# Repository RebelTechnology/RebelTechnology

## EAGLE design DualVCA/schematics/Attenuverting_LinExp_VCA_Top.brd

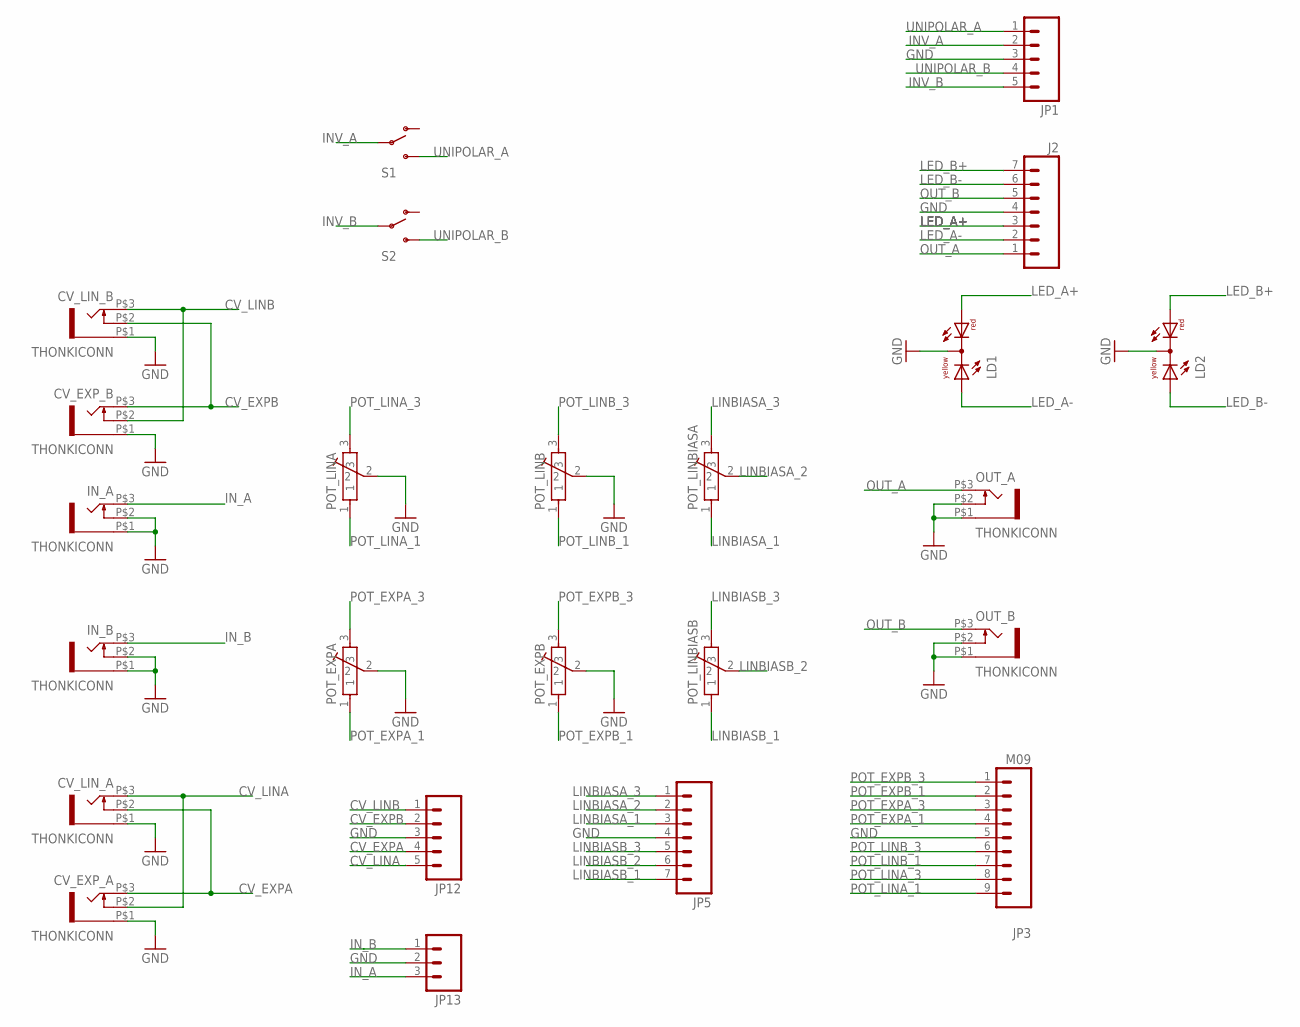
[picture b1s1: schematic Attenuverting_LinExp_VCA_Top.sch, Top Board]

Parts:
CV_EXP_A: THONKICONN
CV_EXP_B: THONKICONN
CV_LIN_A: THONKICONN
CV_LIN_B: THONKICONN
IN_A: THONKICONN
IN_B: THONKICONN
J2: M07; 1X07
JP1, JP12: M05PTH; 1X05
JP3: M09; 1X09
JP5: M07; 1X07
JP13: M03PTH; 1X03
LD1, LD2: DUOLED-RY-C; DUOLED-C-5MM
OUT_A: THONKICONN
OUT_B: THONKICONN
POT_EXPA: POT-ALPS-RK09L1140
POT_EXPB: POT-ALPS-RK09L1140
POT_LINA: POT-ALPS-RK09L1140
POT_LINB: POT-ALPS-RK09L1140
POT_LINBIASA: POT-ALPS-RK09L1140
POT_LINBIASB: POT-ALPS-RK09L1140
S1, S2: SWITCH-SPST; SWITCH-SPDT-SALECOM-T8014

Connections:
CV_EXPA: CV_EXP_A.P$3 (3), CV_LIN_A.P$2 (4), JP12.4
CV_EXPB: CV_EXP_B.P$3 (3), CV_LIN_B.P$2 (4), JP12.2
CV_LINA: CV_EXP_A.P$2 (4), CV_LIN_A.P$3 (3), JP12.5
CV_LINB: CV_EXP_B.P$2 (4), CV_LIN_B.P$3 (3), JP12.1
GND: CV_EXP_A.P$1 (5), CV_EXP_B.P$1 (5), CV_LIN_A.P$1 (5), CV_LIN_B.P$1 (5), IN_A.P$1 (5), IN_A.P$2 (4), IN_B.P$1 (5), IN_B.P$2 (4), J2.4, JP1.3, JP3.5, JP5.4, JP12.3, JP13.2, LD1.C, LD2.C, OUT_A.P$1 (5), OUT_A.P$2 (4), OUT_B.P$1 (5), OUT_B.P$2 (4), POT_EXPA.2, POT_EXPB.2, POT_LINA.2, POT_LINB.2
INV_A: JP1.2, S1.2
INV_B: JP1.5, S2.2
IN_A: IN_A.P$3 (3), JP13.3
IN_B: IN_B.P$3 (3), JP13.1
LED_A+: J2.3, LD1.AR
LED_A-: J2.2, LD1.AX (AY)
LED_B+: J2.7, LD2.AR
LED_B-: J2.6, LD2.AX (AY)
LINBIASA_1: JP5.3, POT_LINBIASA.1
LINBIASA_2: JP5.2, POT_LINBIASA.2
LINBIASA_3: JP5.1, POT_LINBIASA.3
LINBIASB_1: JP5.7, POT_LINBIASB.1
LINBIASB_2: JP5.6, POT_LINBIASB.2
LINBIASB_3: JP5.5, POT_LINBIASB.3
OUT_A: J2.1, OUT_A.P$3 (3)
OUT_B: J2.5, OUT_B.P$3 (3)
POT_EXPA_1: JP3.4, POT_EXPA.1
POT_EXPA_3: JP3.3, POT_EXPA.3
POT_EXPB_1: JP3.2, POT_EXPB.1
POT_EXPB_3: JP3.1, POT_EXPB.3
POT_LINA_1: JP3.9, POT_LINA.1
POT_LINA_3: JP3.8, POT_LINA.3
POT_LINB_1: JP3.7, POT_LINB.1
POT_LINB_3: JP3.6, POT_LINB.3
UNIPOLAR_A: JP1.1, S1.3 (S)
UNIPOLAR_B: JP1.4, S2.3 (S)

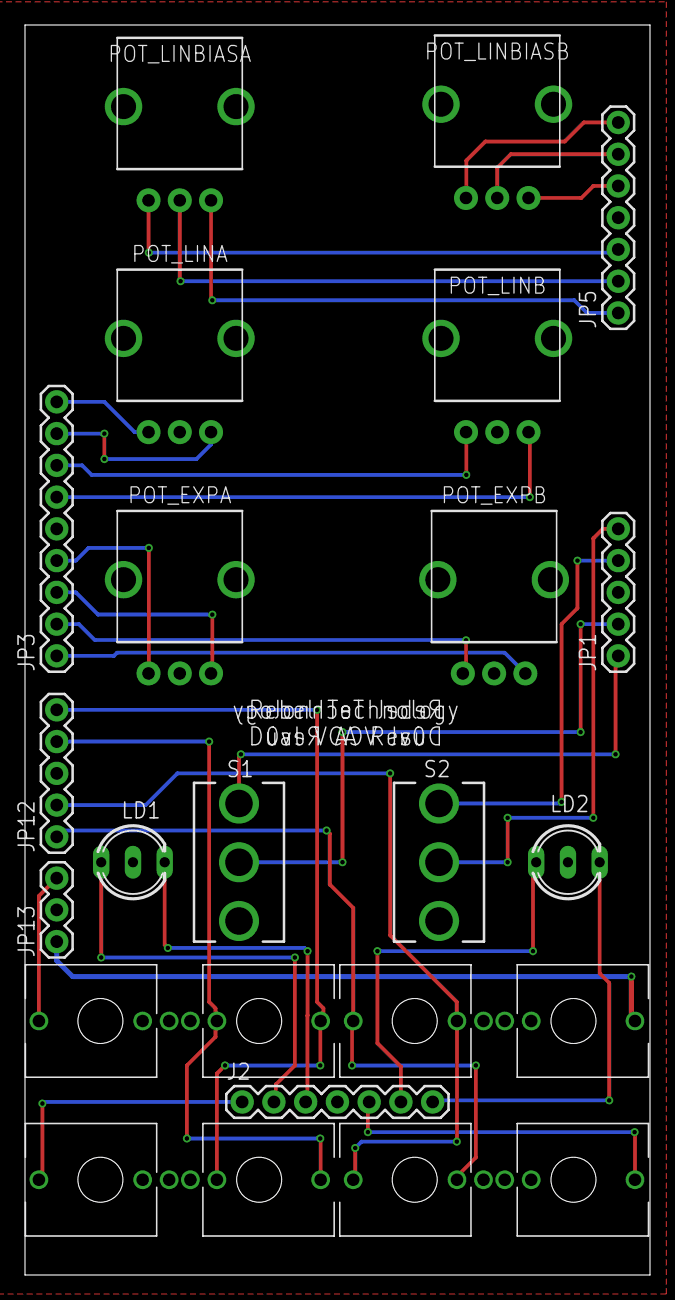
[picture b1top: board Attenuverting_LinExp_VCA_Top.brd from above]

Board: 2 copper layers, 50.0 x 100.0 mm, 24 parts (0 on the bottom side), 31 nets.

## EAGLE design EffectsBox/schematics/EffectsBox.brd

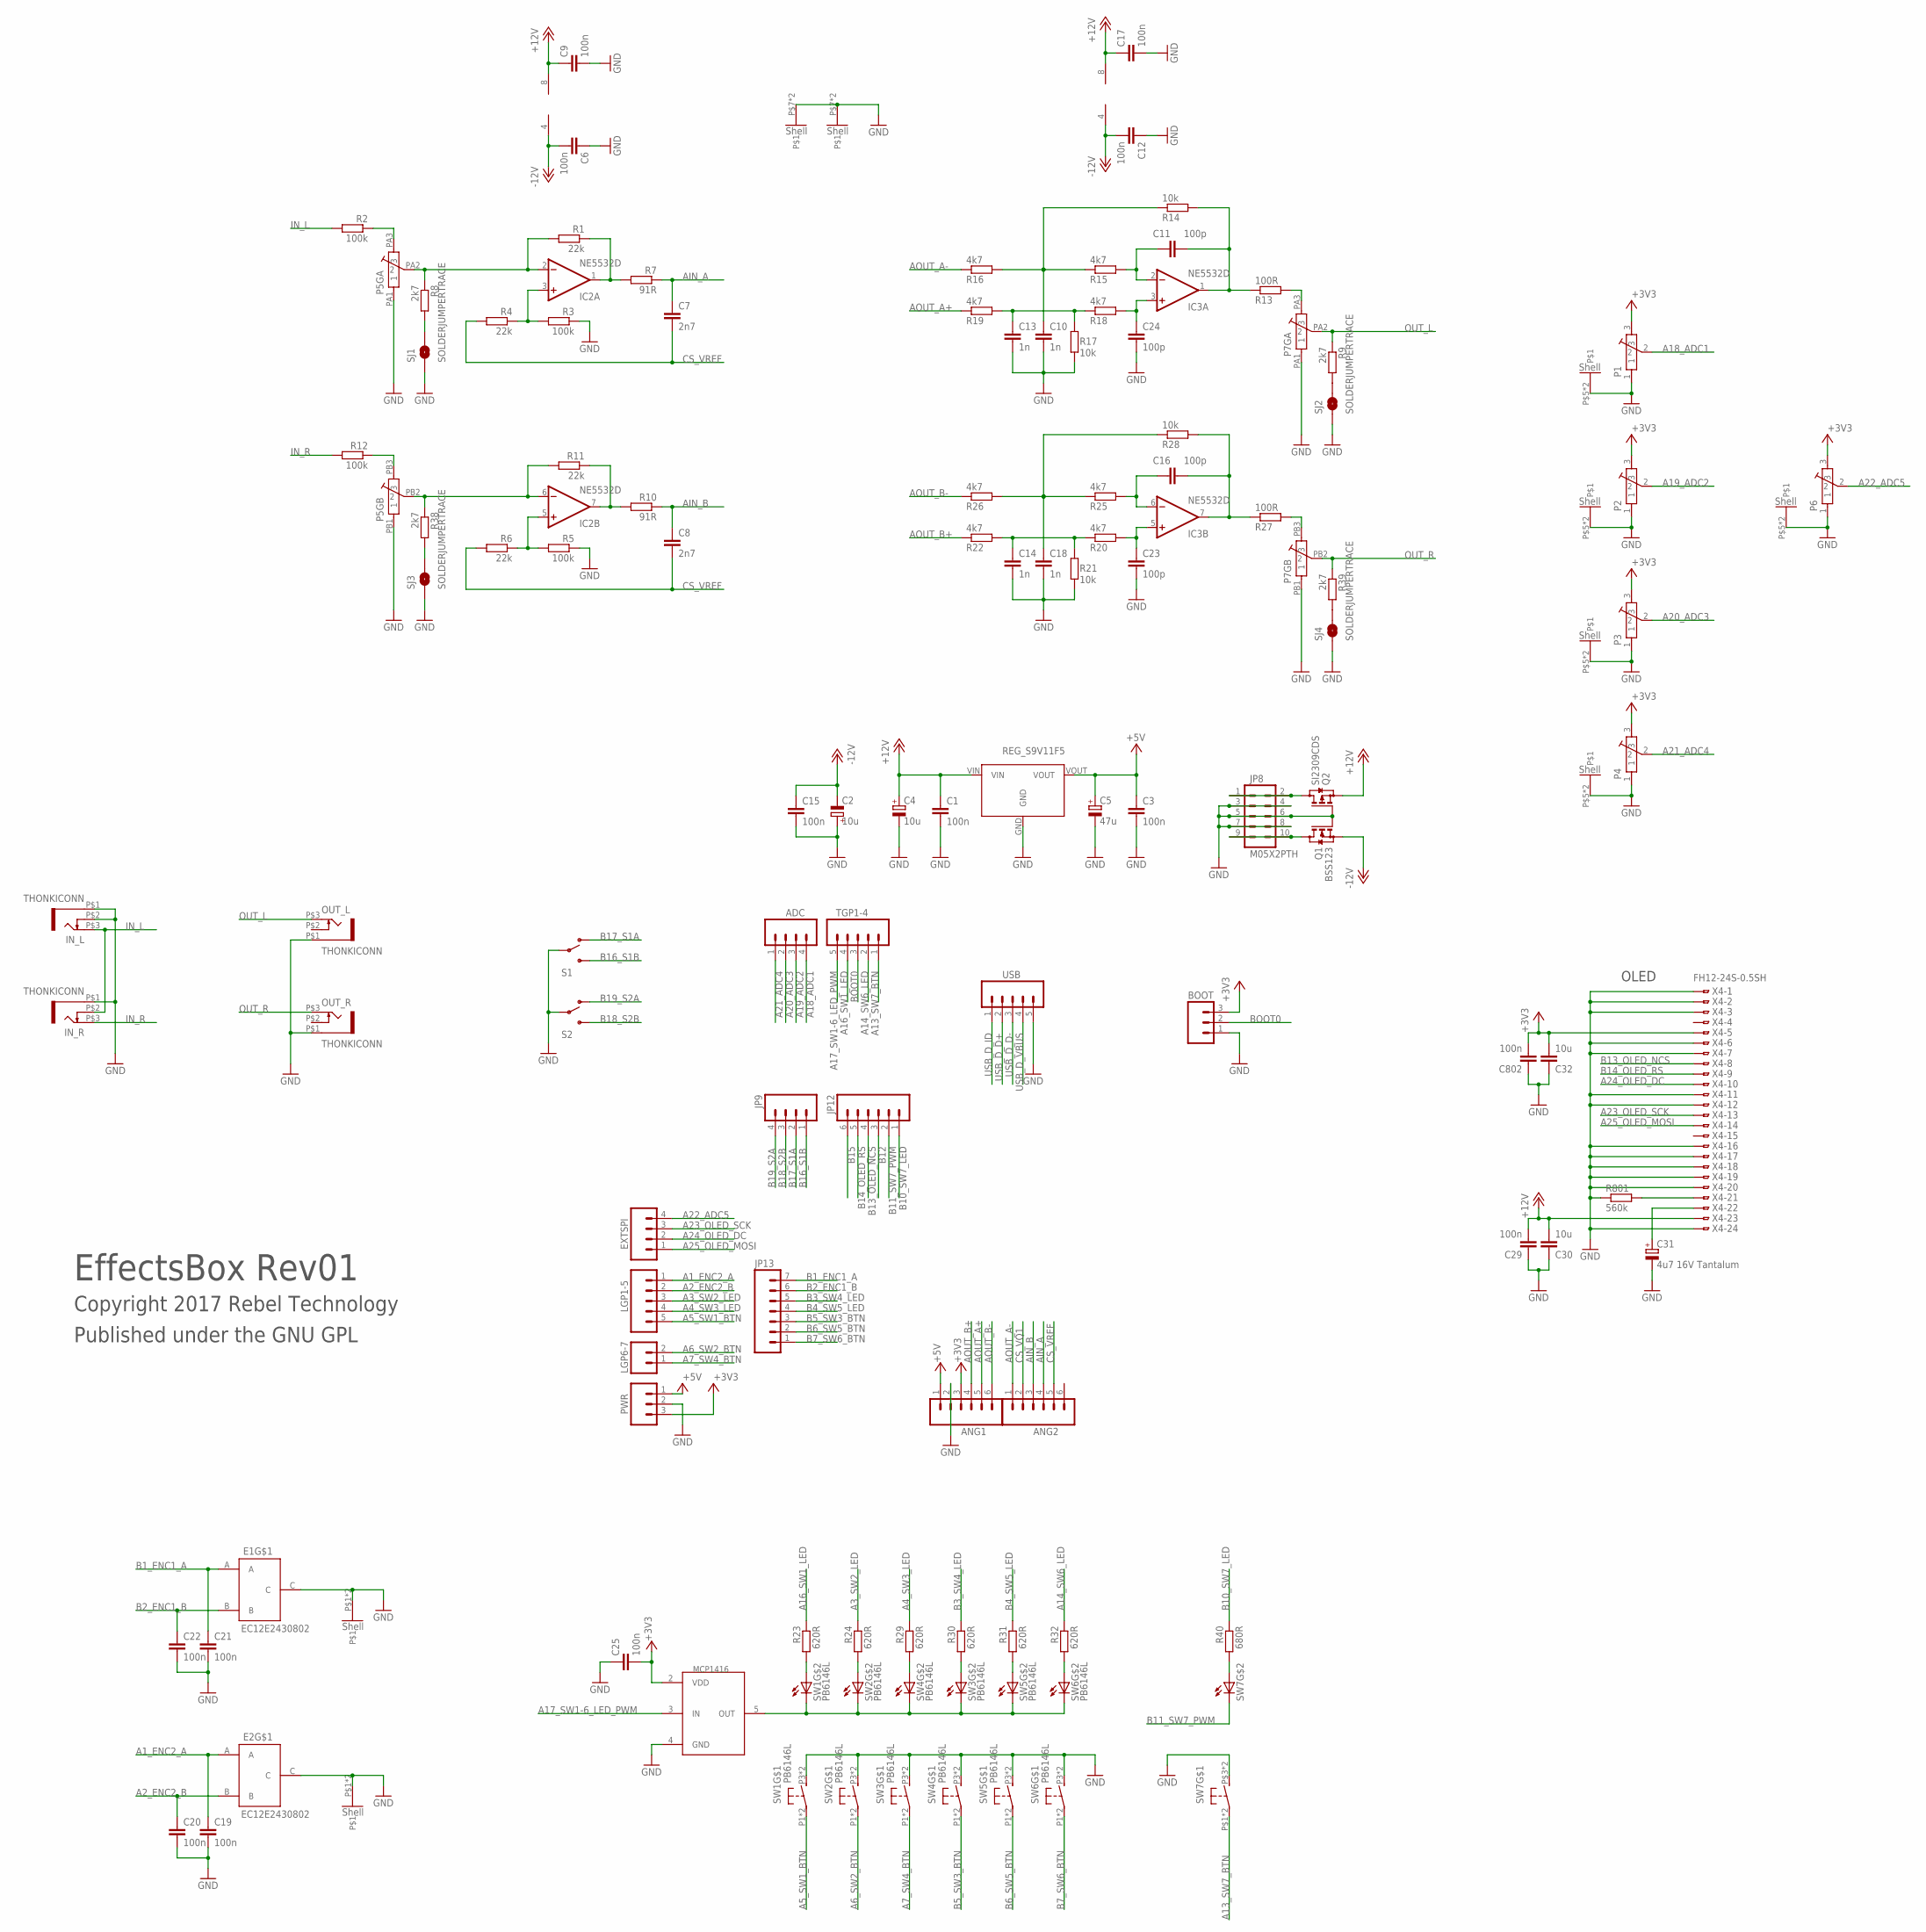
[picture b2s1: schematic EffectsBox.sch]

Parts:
ADC: M04PTH; 1X04
ANG1, ANG2: M06SIP; 1X06
BOOT: M03PTH; 1X03
C1, C3, C6, C9, C12, C15, C17, C19, C20, C21, C22, C25, C29, C802: 100n; C0603
C2, C4: 10u; CPOL-5
C5: 47u; PANASONIC_C
C7, C8: 2n7; C0603
C10, C13, C14, C18: 1n; C0603
C11, C16, C23, C24: 100p; C0603
C30, C32: 10u; C1206
C31: 4u7 16V Tantalum; SMC_A
E1, E2: EC12E2430802
EXTSPI: M04PTH; 1X04
IC2, IC3: NE5532D; SO08
IN_L: THONKICONN
IN_R: THONKICONN
JP8: M05X2PTH; AVR_ICSP
JP9: M04PTH; 1X04
JP12: M06SIP; 1X06
JP13: M07; 1X07
LGP1-5: M05PTH; 1X05
LGP6-7: M02PTH; 1X02
OUT_L: THONKICONN
OUT_R: THONKICONN
P1, P2, P3, P4, P6: POT-ALPS-RK09L1140
P5, P7: POT-ALPS_RK09L12D0A1W; POT-ALPS-RK09L12D0A1W
PWR: M03PTH; 1X03
Q1: BSS123; SOT23
Q2: SI2309CDS; SOT23
R1, R4, R6, R11: 22k; 0603
R2, R3, R5, R12: 100k; 0603
R7, R10: 91R; 0603
R8, R9, R38, R39: 2k7; R0603
R13, R27: 100R; 0603
R14, R17, R21, R28: 10k; 0603
R15, R16, R18, R19, R20, R22, R25, R26: 4k7; 0603
R23, R24, R29, R30, R31, R32: 620R; 0603
R40: 680R; 0603
R801: 560k; 0603
S1, S2: SWITCH-SPST; SWITCH-SPDT-SALECOM-T8014
SJ1, SJ2, SJ3, SJ4: SOLDERJUMPERTRACE; SJ_2S-TRACE
SW1, SW2, SW3, SW4, SW5, SW6: PB6146L
SW7: KS01-BL
TGP1-4: M05PTH; 1X05
U1: REG_S9V11F5
U2: MCP1416; SOT23-5
USB: M05PTH; 1X05
X4: FH12-24S-0.5SH

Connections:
+3V3: ANG1.3, BOOT.3, C25.2, C32.2, C802.2, P1.3, P2.3, P3.3, P4.3, P6.3, PWR.3, U2.2 (VDD), X4.5
+5V: ANG1.1, C3.1, C5.+, PWR.1, U1.VOUT
+12V: C1.1, C4.+, C9.1, C17.1, C29.2, C30.2, IC2.8 (V+), IC3.8 (V+), Q2.2 (S), U1.VIN, X4.23
-12V: C2.-, C6.2, C12.2, C15.1, IC2.4 (V-), IC3.4 (V-), Q1.2 (S)
A1_ENC2_A: C19.1, E2.A, LGP1-5.1
A2_ENC2_B: C20.1, E2.B, LGP1-5.2
A3_SW2_LED: LGP1-5.3, R24.1
A4_SW3_LED: LGP1-5.4, R29.1
A5_SW1_BTN: LGP1-5.5, SW1.P1, SW1.P2
A6_SW2_BTN: LGP6-7.2, SW2.P1, SW2.P2
A7_SW4_BTN: LGP6-7.1, SW3.P1, SW3.P2
A13_SW7_BTN: SW7.P$1, SW7.P$2, TGP1-4.1
A14_SW6_LED: R32.1, TGP1-4.2
A16_SW1_LED: R23.1, TGP1-4.4
A17_SW1-6_LED_PWM: TGP1-4.5, U2.3 (IN)
A18_ADC1: ADC.4, P1.2
A19_ADC2: ADC.3, P2.2
A20_ADC3: ADC.2, P3.2
A21_ADC4: ADC.1, P4.2
A22_ADC5: EXTSPI.4, P6.2
A23_OLED_SCK: EXTSPI.3, X4.13
A24_OLED_DC: EXTSPI.2, X4.10
A25_OLED_MOSI: EXTSPI.1, X4.14
AIN_A: ANG2.4, C7.1, R7.1
AIN_B: ANG2.3, C8.1, R10.1
AOUT_A+: ANG1.5, R19.1
AOUT_A-: ANG2.1, R16.1
AOUT_B+: ANG1.4, R22.1
AOUT_B-: ANG1.6, R26.1
B1_ENC1_A: C21.1, E1.A, JP13.7
B2_ENC1_B: C22.1, E1.B, JP13.6
B3_SW4_LED: JP13.5, R30.1
B4_SW5_LED: JP13.4, R31.1
B5_SW3_BTN: JP13.3, SW4.P1, SW4.P2
B6_SW5_BTN: JP13.2, SW5.P1, SW5.P2
B7_SW6_BTN: JP13.1, SW6.P1, SW6.P2
B10_SW7_LED: JP12.1, R40.1
B11_SW7_PWM: JP12.2, SW7.P$C (C)
B12: JP12.3
B13_OLED_NCS: JP12.4, X4.8
B14_OLED_RS: JP12.5, X4.9
B15: JP12.6
B16_S1B: JP9.1, S1.3 (S)
B17_S1A: JP9.2, S1.1 (O)
B18_S2B: JP9.3, S2.3 (S)
B19_S2A: JP9.4, S2.1 (O)
BOOT0: BOOT.2, TGP1-4.3
CS_VQ1: ANG2.2
CS_VREF: ANG2.5, C7.2, C8.2, R4.2, R6.2
GND: ANG1.2, BOOT.1, C1.2, C2.+, C3.2, C4.-, C5.-, C6.1, C9.2, C10.2, C12.1, C13.2, C14.2, C15.2, C17.2, C18.2, C19.2, C20.2, C21.2, C22.2, C23.1, C24.1, C25.1, C29.1, C30.1, C31.-, C32.1, C802.1, E1.C, E1.P$1, E1.P$2, E2.C, E2.P$1, E2.P$2, IN_L.P$1 (5), IN_L.P$2 (4), IN_R.P$1 (5), JP8.3, JP8.4, JP8.5, JP8.6, JP8.7, JP8.8, OUT_L.P$1 (5), OUT_R.P$1 (5), P1.1, P1.P$5, P1.P$6, P2.1, P2.P$5, P2.P$6, P3.1, P3.P$5, P3.P$6, P4.1, P4.P$5, P4.P$6, P5.P$7, P5.P$8, P5.PA1 (1), P5.PB1 (1), P6.1, P6.P$5, P6.P$6, P7.P$7, P7.P$8, P7.PA1 (1), P7.PB1 (1), PWR.2, Q1.1 (G), Q2.1 (G), R3.1, R5.1, R17.1, R21.1, R801.1, S1.2, S2.2, SJ1.1, SJ2.1, SJ3.1, SJ4.1, SW1.P3 (S), SW1.P4 (S), SW2.P3 (S), SW2.P4 (S), SW3.P3 (S), SW3.P4 (S), SW4.P3 (S), SW4.P4 (S), SW5.P3 (S), SW5.P4 (S), SW6.P3 (S), SW6.P4 (S), SW7.P$3 (S), SW7.P$4 (S), U1.GND, U2.4 (GND), USB.5, X4.1, X4.2, X4.3, X4.6, X4.7, X4.11, X4.12, X4.16, X4.17, X4.18, X4.19, X4.20, X4.24
IN_L: IN_L.P$3 (3), IN_R.P$2 (4), R2.2
IN_R: IN_R.P$3 (3), R12.2
unnamed: IC2.1 (OUT), R1.1, R7.2
unnamed: IC2.3 (+IN), R3.2, R4.1
unnamed: P5.PA3 (3), R2.1
unnamed: IC2.5 (+IN), R5.2, R6.1
unnamed: C31.+, X4.22
unnamed: P7.PA3 (3), R13.2
unnamed: C11.1, IC3.2 (-IN), R15.2
unnamed: JP8.9, JP8.10, Q1.3 (D)
unnamed: IC2.2 (-IN), P5.PA2 (2), R1.2, R8.1
unnamed: IC2.7 (OUT), R10.2, R11.1
unnamed: C24.2, IC3.3 (+IN), R18.2
unnamed: JP8.1, JP8.2, Q2.3 (D)
unnamed: R9.2, SJ2.2
unnamed: SW1.PL2 (C), SW2.PL2 (C), SW3.PL2 (C), SW4.PL2 (C), SW5.PL2 (C), SW6.PL2 (C), U2.5 (OUT)
unnamed: C13.1, R17.2, R18.1, R19.2
unnamed: R23.2, SW1.PL1 (A)
unnamed: R8.2, SJ1.2
unnamed: C16.2, IC3.7 (OUT), R27.1, R28.2
unnamed: R24.2, SW2.PL1 (A)
unnamed: R29.2, SW4.PL1 (A)
unnamed: R30.2, SW3.PL1 (A)
unnamed: R31.2, SW5.PL1 (A)
unnamed: R32.2, SW6.PL1 (A)
unnamed: C18.1, R25.1, R26.2, R28.1
unnamed: R801.2, X4.21
unnamed: C16.1, IC3.6 (-IN), R25.2
unnamed: C23.2, IC3.5 (+IN), R20.2
unnamed: IC2.6 (-IN), P5.PB2 (2), R11.2, R38.1
unnamed: C14.1, R20.1, R21.2, R22.2
unnamed: P5.PB3 (3), R12.1
unnamed: R38.2, SJ3.2
unnamed: P7.PB3 (3), R27.2
unnamed: R39.2, SJ4.2
unnamed: C11.2, IC3.1 (OUT), R13.1, R14.2
unnamed: C10.1, R14.1, R15.1, R16.2
OUT_L: OUT_L.P$3 (3), P7.PA2 (2), R9.1
OUT_R: OUT_R.P$3 (3), P7.PB2 (2), R39.1
SW6_LED: R40.2, SW7.P$A (A)
USB_D_D+: USB.2
USB_D_D-: USB.3
USB_D_ID: USB.1
USB_D_VBUS: USB.4

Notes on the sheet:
EffectsBox Rev01
Copyright 2017 Rebel Technology
Published under the GNU GPL
OLED

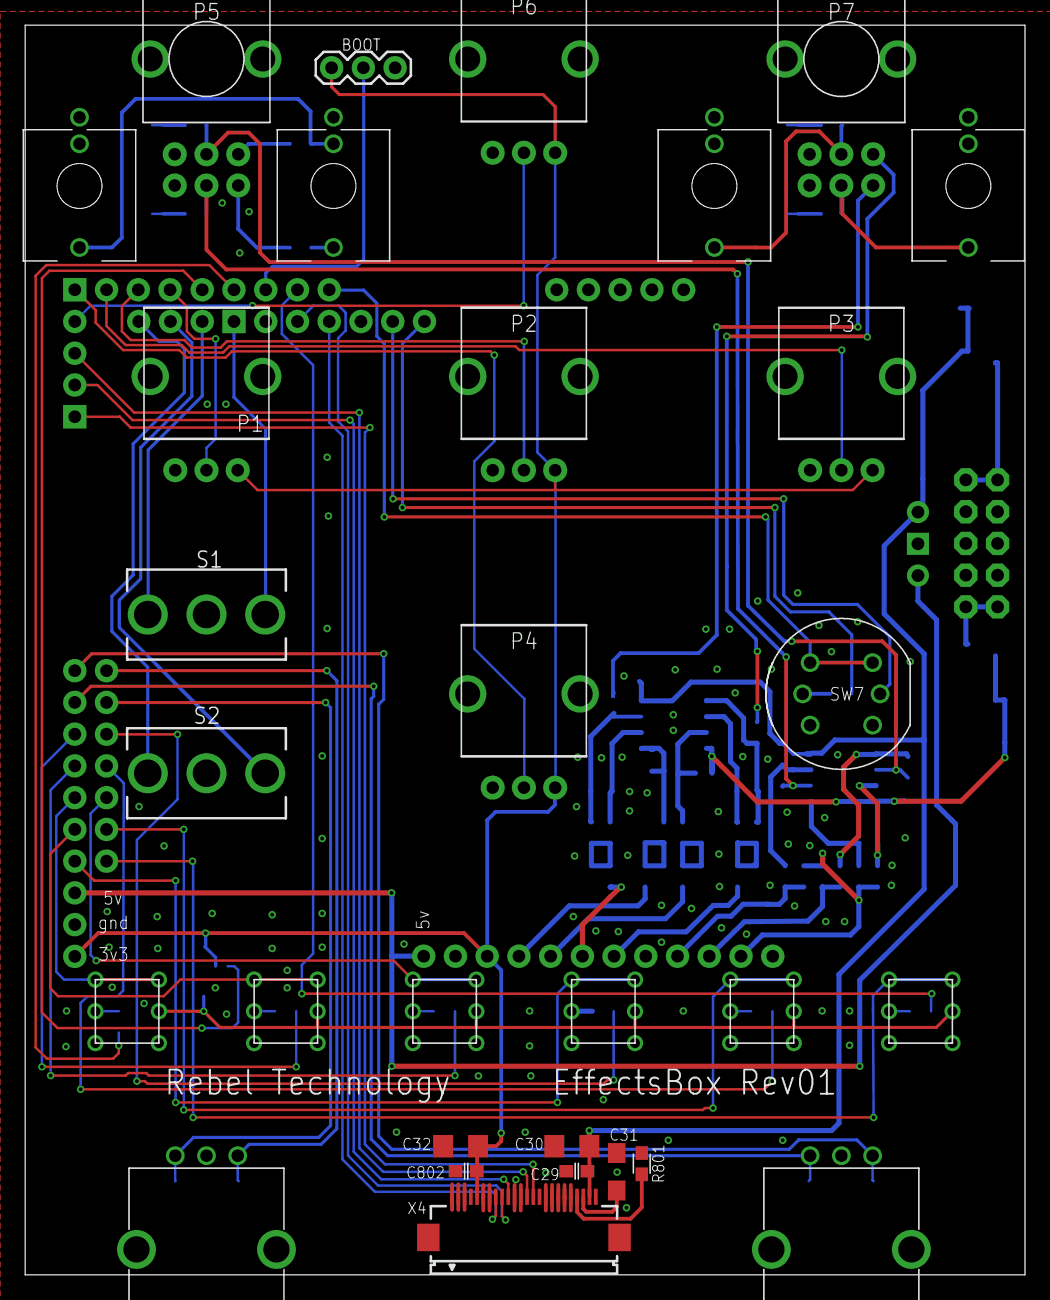
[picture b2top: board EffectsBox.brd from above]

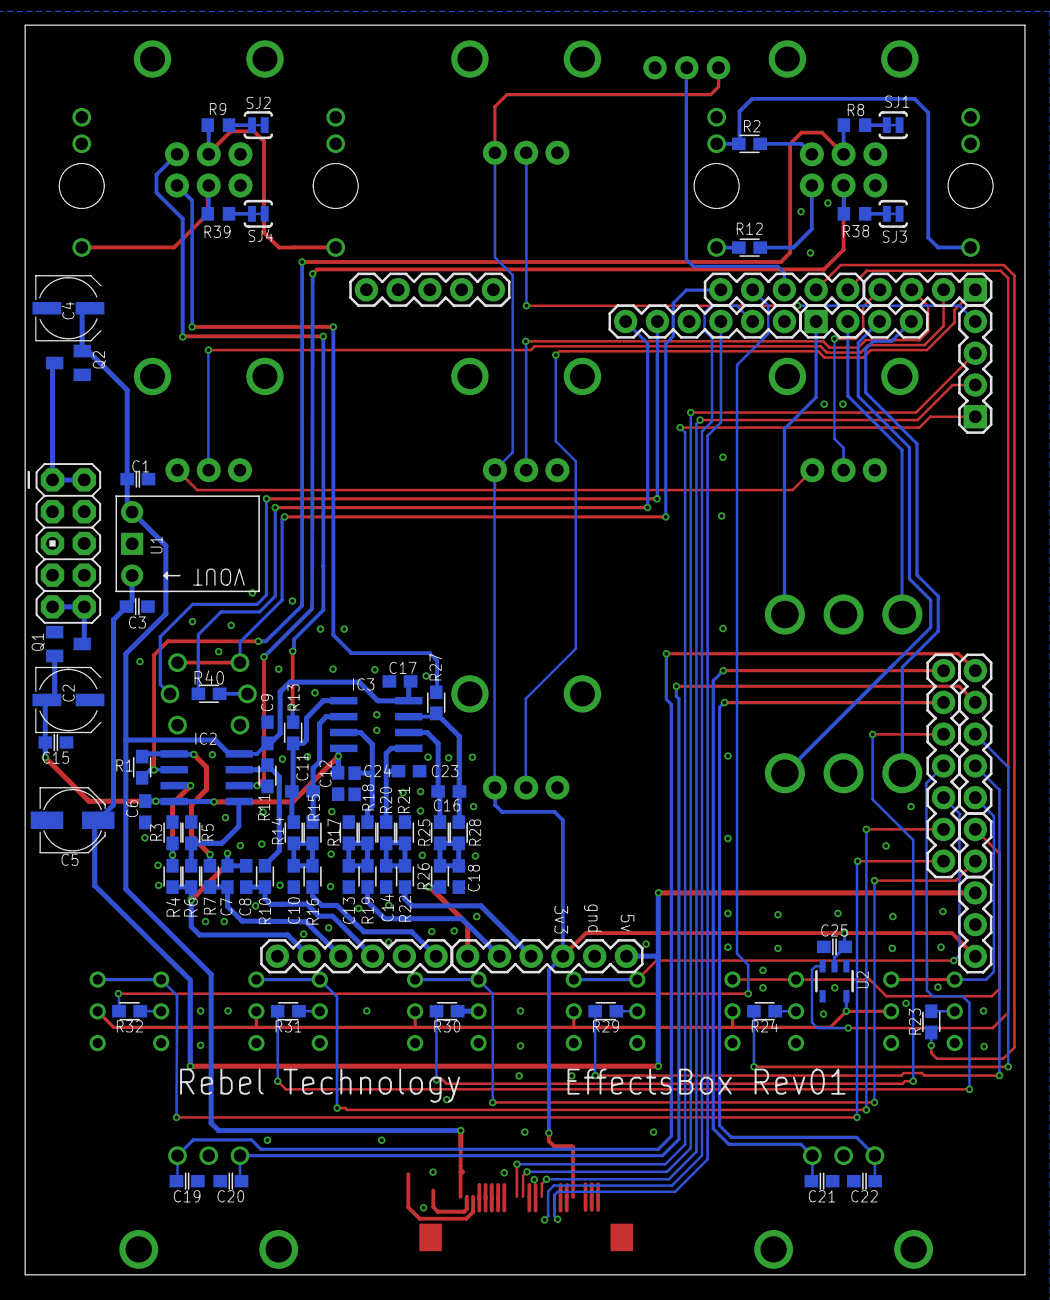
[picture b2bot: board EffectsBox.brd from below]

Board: 2 copper layers, 80.0 x 100.0 mm, 113 parts (83 on the bottom side), 87 nets.

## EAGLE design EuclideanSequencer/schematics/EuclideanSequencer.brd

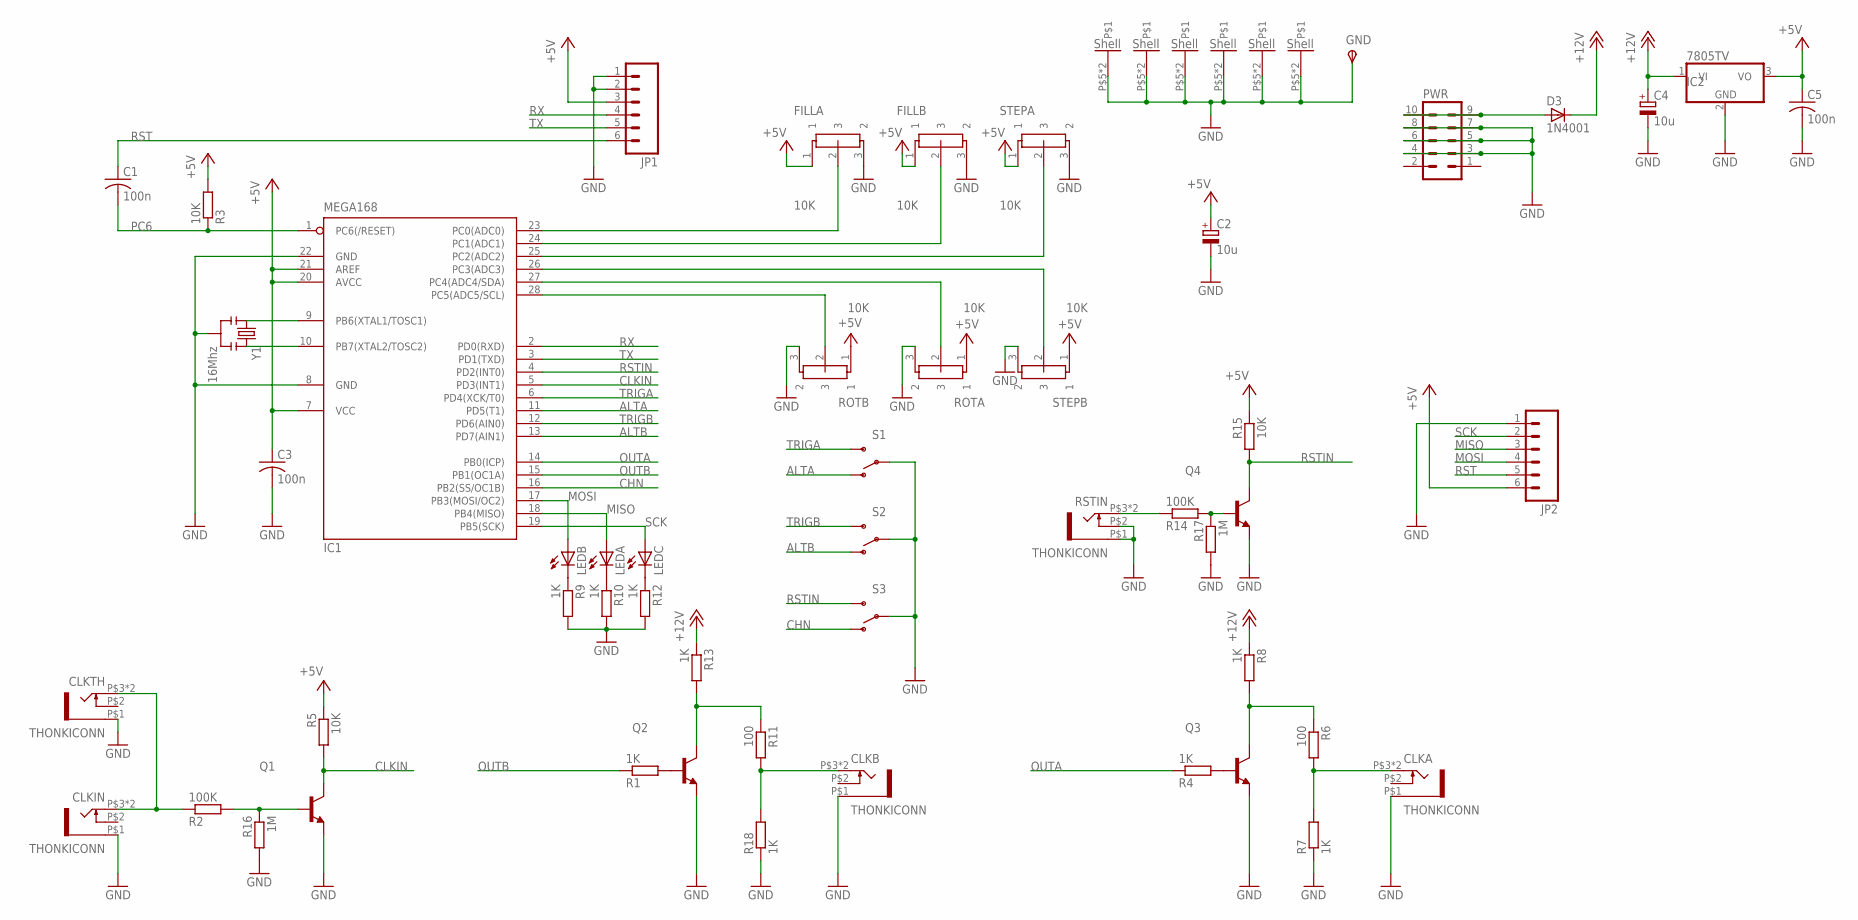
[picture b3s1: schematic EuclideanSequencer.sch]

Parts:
C1, C3, C5: 100n; C050-024X044
C2, C4: 10u; E5-6
CLKA: THONKICONN
CLKB: THONKICONN
CLKIN: THONKICONN
CLKTH: THONKICONN
D3: 1N4001; DIODE-1N4001
FILLA: 10K; POT-ALPS-RK09L1140
FILLB: 10K; POT-ALPS-RK09L1140
GND: TPSPAD1-20; P1-20
IC1: MEGA168; DIL28-3
IC2: 7805TV; TO220V
JP1, JP2: M06SIP; 1X06
LEDA: LED3MM
LEDB: LED3MM
LEDC: LED3MM
PWR: MA05-2
Q1, Q2, Q3, Q4: 2N3904-NPN-TO92-EBC; TO92-EBC
R1, R4, R7, R8, R9, R10, R12, R13, R18: 1K; 0204/7
R2, R14: 100K; 0204/7
R3, R5, R15: 10K; 0204/7
R6, R11: 100; 0204/7
R16, R17: 1M; 0204/7
ROTA: 10K; POT-ALPS-RK09L1140
ROTB: 10K; POT-ALPS-RK09L1140
RSTIN: THONKICONN
S1, S2, S3: SWITCH-SPST; SWITCH-SPDT-SALECOM-T8014
STEPA: 10K; POT-ALPS-RK09L1140
STEPB: 10K; POT-ALPS-RK09L1140
Y1: 16Mhz; RESONATOR-PTH

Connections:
ALTA: IC1.11 (PD5(T1)), S1.1 (O)
ALTB: IC1.13 (PD7(AIN1)), S2.1 (O)
CHN: IC1.16 (PB2(SS/OC1B)), S3.1 (O)
CLKIN: IC1.5 (PD3(INT1)), Q1.C, R5.2
FILFB: FILLB.2 (3), IC1.24 (PC1(ADC1))
GND: C2.-, C3.2, C4.-, C5.2, CLKA.P$1 (5), CLKB.P$1 (5), CLKIN.P$1 (5), CLKTH.P$1 (5), FILLA.3 (2), FILLA.P$5, FILLA.P$6, FILLB.3 (2), FILLB.P$5, FILLB.P$6, GND.TP, IC1.8 (GND), IC1.22 (GND), IC2.2 (GND), JP1.1, JP1.2, JP2.1, PWR.3, PWR.4, PWR.5, PWR.6, PWR.7, PWR.8, Q1.E, Q2.E, Q3.E, Q4.E, R7.1, R9.2, R10.2, R12.2, R16.2, R17.2, R18.1, ROTA.3 (2), ROTA.P$5, ROTA.P$6, ROTB.3 (2), ROTB.P$5, ROTB.P$6, RSTIN.P$1 (5), RSTIN.P$2 (4), S1.2, S2.2, S3.2, STEPA.3 (2), STEPA.P$5, STEPA.P$6, STEPB.3 (2), STEPB.P$5, STEPB.P$6, Y1.2
MISO: IC1.18 (PB4(MISO)), JP2.3, LEDA.A
MOSI: IC1.17 (PB3(MOSI/OC2)), JP2.4, LEDB.A
unnamed: FILLA.2 (3), IC1.23 (PC0(ADC0))
unnamed: IC1.25 (PC2(ADC2)), STEPA.2 (3)
unnamed: IC1.26 (PC3(ADC3)), STEPB.2 (3)
unnamed: IC1.27 (PC4(ADC4/SDA)), ROTA.2 (3)
unnamed: IC1.28 (PC5(ADC5/SCL)), ROTB.2 (3)
unnamed: IC1.9 (PB6(XTAL1/TOSC1)), Y1.1
unnamed: IC1.10 (PB7(XTAL2/TOSC2)), Y1.3
unnamed: CLKB.P$3 (3), CLKB.P$4 (3), R11.2, R18.2
unnamed: Q2.C, R11.1, R13.2
unnamed: Q1.B, R2.2, R16.1
unnamed: CLKIN.P$3 (3), CLKIN.P$4 (3), CLKTH.P$3 (3), CLKTH.P$4 (3), R2.1
unnamed: R14.1, RSTIN.P$3 (3), RSTIN.P$4 (3)
unnamed: Q2.B, R1.2
unnamed: LEDB.K (C), R9.1
unnamed: Q3.B, R4.2
unnamed: CLKA.P$3 (3), CLKA.P$4 (3), R6.2, R7.2
unnamed: Q3.C, R6.1, R8.2
unnamed: LEDA.K (C), R10.1
unnamed: LEDC.K (C), R12.1
unnamed: Q4.B, R14.2, R17.1
unnamed: D3.A, PWR.9, PWR.10
OUTA: IC1.14 (PB0(ICP)), R4.1
OUTB: IC1.15 (PB1(OC1A)), R1.1
PC6: C1.2, IC1.1 (PC6(/RESET)), R3.1
RST: C1.1, JP1.6, JP2.5
RSTIN: IC1.4 (PD2(INT0)), Q4.C, R15.2, S3.3 (S)
RX: IC1.2 (PD0(RXD)), JP1.4
SCK: IC1.19 (PB5(SCK)), JP2.2, LEDC.A
TRIGA: IC1.6 (PD4(XCK/T0)), S1.3 (S)
TRIGB: IC1.12 (PD6(AIN0)), S2.3 (S)
TX: IC1.3 (PD1(TXD)), JP1.5

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
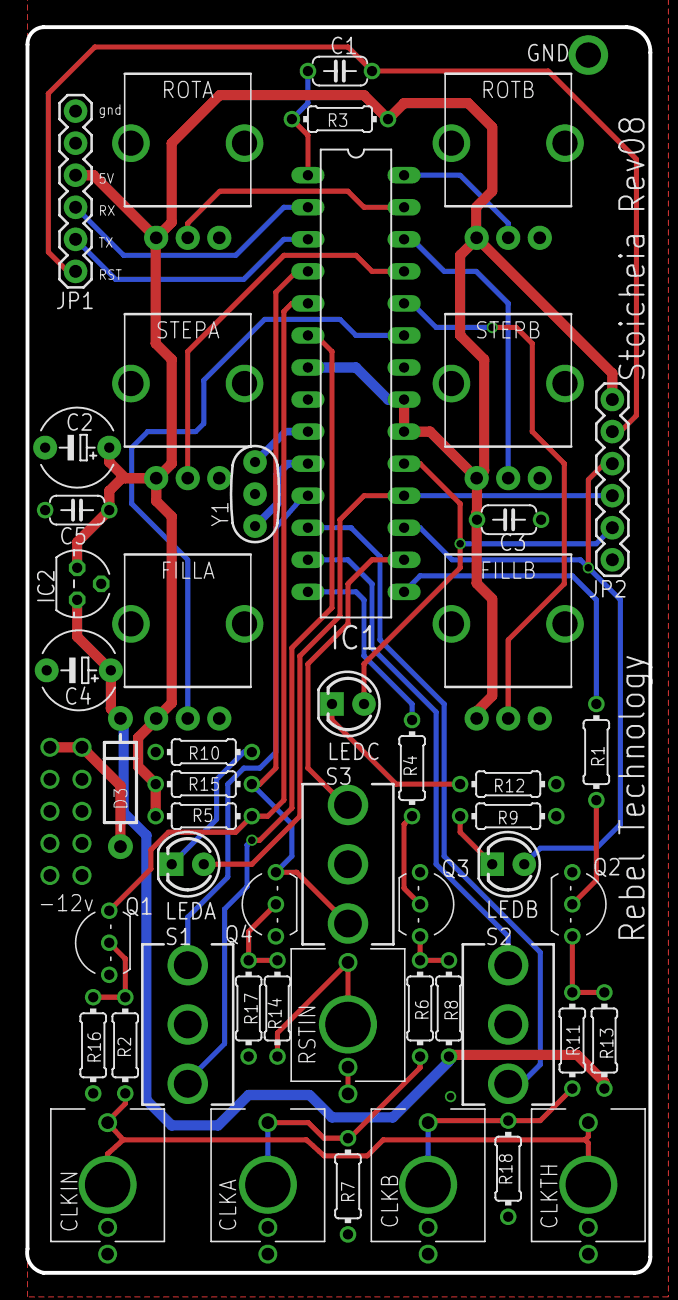
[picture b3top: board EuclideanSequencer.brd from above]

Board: 2 copper layers, 49.4 x 98.7 mm, 52 parts (1 on the bottom side), 41 nets.

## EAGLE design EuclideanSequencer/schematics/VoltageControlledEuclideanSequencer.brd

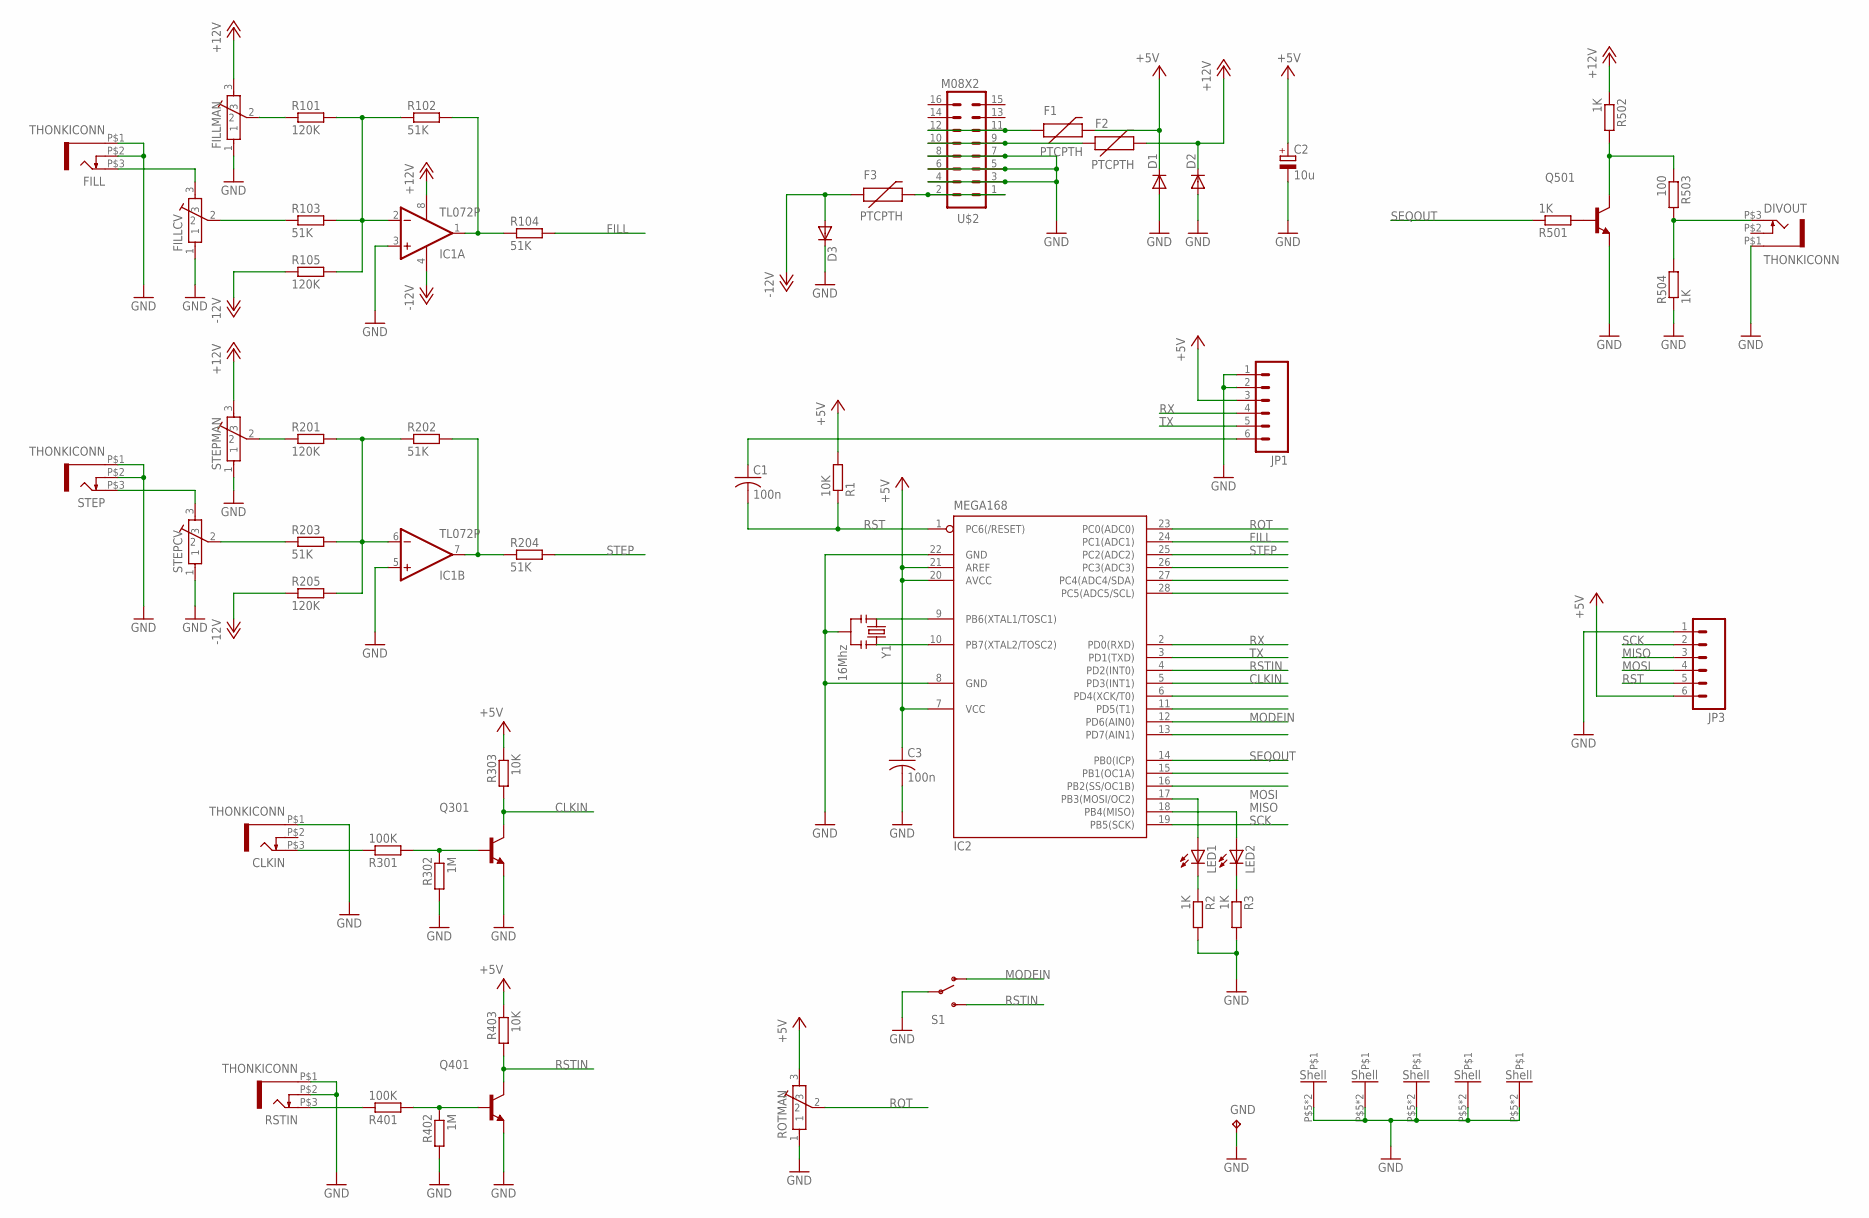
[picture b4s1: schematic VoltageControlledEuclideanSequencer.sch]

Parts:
C1, C3: 100n; C050-024X044
C2: 10u; E2,5-6
CLKIN: THONKICONN
D1, D2, D3: DIODE1N4001; DIODE-1N4001
DIVOUT: THONKICONN
F1, F2, F3: PTCPTH; PTC
FILL: THONKICONN
FILLCV: POT-ALPS-RK09L1140
FILLMAN: POT-ALPS-RK09L1140
GND: TPPAD1-20; P1-20
IC1: TL072P; DIL08
IC2: MEGA168; DIL28-3
JP1, JP3: M06SIP; 1X06
LED1, LED2: LED3MM
Q301, Q401, Q501: 2N3904-NPN-TO92-EBC; TO92-EBC
R1, R303, R403: 10K; 0204/7
R2, R3, R501, R502, R504: 1K; 0204/7
R101, R105, R201, R205: 120K; 0204/7
R102, R103, R104, R202, R203, R204: 51K; 0204/7
R301, R401: 100K; 0204/7
R302, R402: 1M; 0204/7
R503: 100; 0204/7
ROTMAN: POT-ALPS-RK09L1140
RSTIN: THONKICONN
S1: SWITCH-SPST; SWITCH-SPDT-SALECOM-T8014
STEP: THONKICONN
STEPCV: POT-ALPS-RK09L1140
STEPMAN: POT-ALPS-RK09L1140
U$2: M08X2; 2X8
Y1: 16Mhz; RESONATOR-PTH

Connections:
+5V: C2.+, C3.1, D1.C, F1.P$2 (2), IC2.7 (VCC), IC2.20 (AVCC), IC2.21 (AREF), JP1.3, JP3.6, R1.2, R303.1, R403.1, ROTMAN.3
+12V: D2.C, F2.P$2 (2), FILLMAN.3, IC1.8 (V+), R502.1, STEPMAN.3
-12V: D3.A, F3.P$1 (1), IC1.4 (V-), R105.1, R205.1
ALT: IC2.11 (PD5(T1))
CLKIN: IC2.5 (PD3(INT1)), Q301.C, R303.2
CMBOUT: IC2.16 (PB2(SS/OC1B))
DELOUT: IC2.15 (PB1(OC1A))
FILL: IC2.24 (PC1(ADC1)), R104.2
GND: C2.-, C3.2, CLKIN.P$1 (5), D1.A, D2.A, D3.C, DIVOUT.P$1 (5), FILL.P$1 (5), FILL.P$2 (4), FILLCV.1, FILLCV.P$5, FILLCV.P$6, FILLMAN.1, FILLMAN.P$5, FILLMAN.P$6, GND.TP, IC1.3 (+IN), IC1.5 (+IN), IC2.8 (GND), IC2.22 (GND), JP1.1, JP1.2, JP3.1, Q301.E, Q401.E, Q501.E, R2.2, R3.2, R302.2, R402.2, R504.1, ROTMAN.1, ROTMAN.P$5, ROTMAN.P$6, RSTIN.P$1 (5), RSTIN.P$2 (4), S1.2, STEP.P$1 (5), STEP.P$2 (4), STEPCV.1, STEPCV.P$5, STEPCV.P$6, STEPMAN.1, STEPMAN.P$5, STEPMAN.P$6, U$2.3, U$2.4, U$2.5, U$2.6, U$2.7, U$2.8, Y1.2
MISO: IC2.18 (PB4(MISO)), JP3.3, LED2.A
MODEB: IC2.13 (PD7(AIN1))
MODEIN: IC2.12 (PD6(AIN0)), S1.1 (O)
MOSI: IC2.17 (PB3(MOSI/OC2)), JP3.4, LED1.A
unnamed: FILL.P$3 (3), FILLCV.3
unnamed: IC1.2 (-IN), R101.2, R102.1, R103.2, R105.2
unnamed: FILLMAN.2, R101.1
unnamed: IC1.1 (OUT), R102.2, R104.1
unnamed: FILLCV.2, R103.1
unnamed: F3.P$2 (2), U$2.1, U$2.2
unnamed: IC1.6 (-IN), R201.2, R202.1, R203.2, R205.2
unnamed: R201.1, STEPMAN.2
unnamed: IC1.7 (OUT), R202.2, R204.1
unnamed: R203.1, STEPCV.2
unnamed: STEP.P$3 (3), STEPCV.3
unnamed: IC2.9 (PB6(XTAL1/TOSC1)), Y1.1
unnamed: IC2.10 (PB7(XTAL2/TOSC2)), Y1.3
unnamed: LED1.K (C), R2.1
unnamed: LED2.K (C), R3.1
unnamed: Q301.B, R301.2, R302.1
unnamed: CLKIN.P$3 (3), R301.1
unnamed: C1.1, JP1.6
unnamed: Q401.B, R401.2, R402.1
unnamed: Q501.B, R501.2
unnamed: DIVOUT.P$3 (3), R503.2, R504.2
unnamed: Q501.C, R502.2, R503.1
unnamed: R401.1, RSTIN.P$3 (3)
unnamed: F1.P$1 (1), U$2.11, U$2.12
unnamed: F2.P$1 (1), U$2.9, U$2.10
ROT: IC2.23 (PC0(ADC0)), ROTMAN.2
RST: C1.2, IC2.1 (PC6(/RESET)), JP3.5, R1.1
RSTIN: IC2.4 (PD2(INT0)), Q401.C, R403.2, S1.3 (S)
RX: IC2.2 (PD0(RXD)), JP1.4
SCK: IC2.19 (PB5(SCK)), JP3.2
SEQOUT: IC2.14 (PB0(ICP)), R501.1
STEP: IC2.25 (PC2(ADC2)), R204.2
TRIG: IC2.6 (PD4(XCK/T0))
TX: IC2.3 (PD1(TXD)), JP1.5

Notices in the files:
parts and their libraries:
SparkFun: Licensing: CC v3.0 Share-Alike You are welcome to use this library for commercial purposes.
